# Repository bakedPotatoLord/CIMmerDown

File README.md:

# CIMmer Down
A project to control 2 drive 2 rev robotics spark ESCs from an arduino nano. 

Coming out of a desire to make use of obsolete parts used by FIRST robotics teams worldwide, we designed a low-cost open source electric longboard. Designed to be accessible to high-school and college students to build, using mostly 3d printed and COTS parts, this project aims to provide an interesting and fun entry into the world of RF electronics, motor control, urethane molding, and more. 

Documentation/Development are not yet complete. Help is always appreciated.

## Features
- Handheld remote
- Status LED
- 2 speed modes
- 16mph top speed
- People of the oposite sex may find you more attractive.
- Disconnection detection and e-stop safety.

## More Details

further, yet incomplete documentation can be found at these pages:

- [Electronics](/Electronics.md)
- [Manufacturing](/Manufacturing.md)

## Selected Media

## Why is is called that?
the `CIM` from CIMmer down is a reference to FRC [CIM](https://andymark.com/products/2-5-in-cim-motor) motor.

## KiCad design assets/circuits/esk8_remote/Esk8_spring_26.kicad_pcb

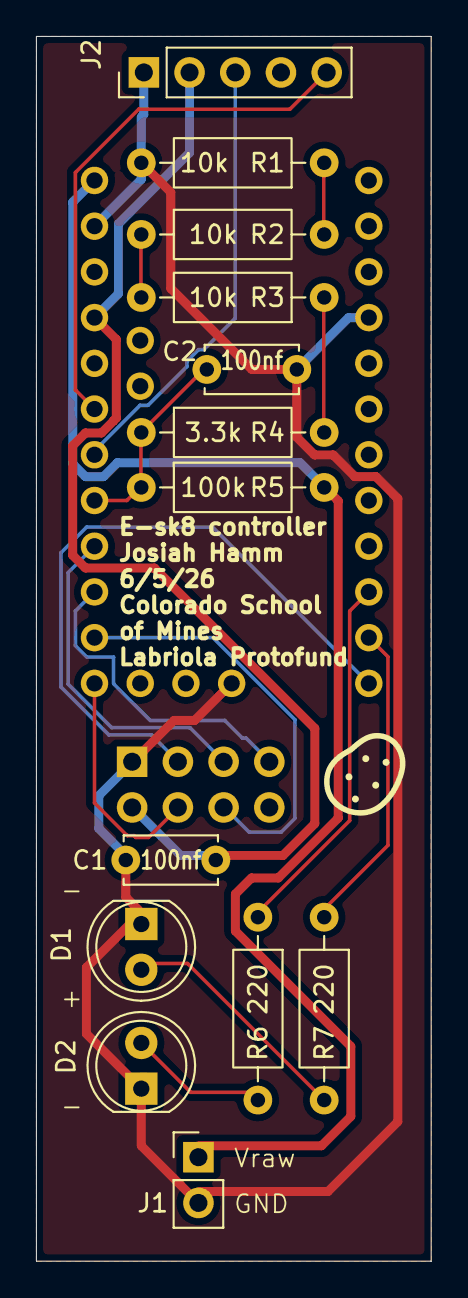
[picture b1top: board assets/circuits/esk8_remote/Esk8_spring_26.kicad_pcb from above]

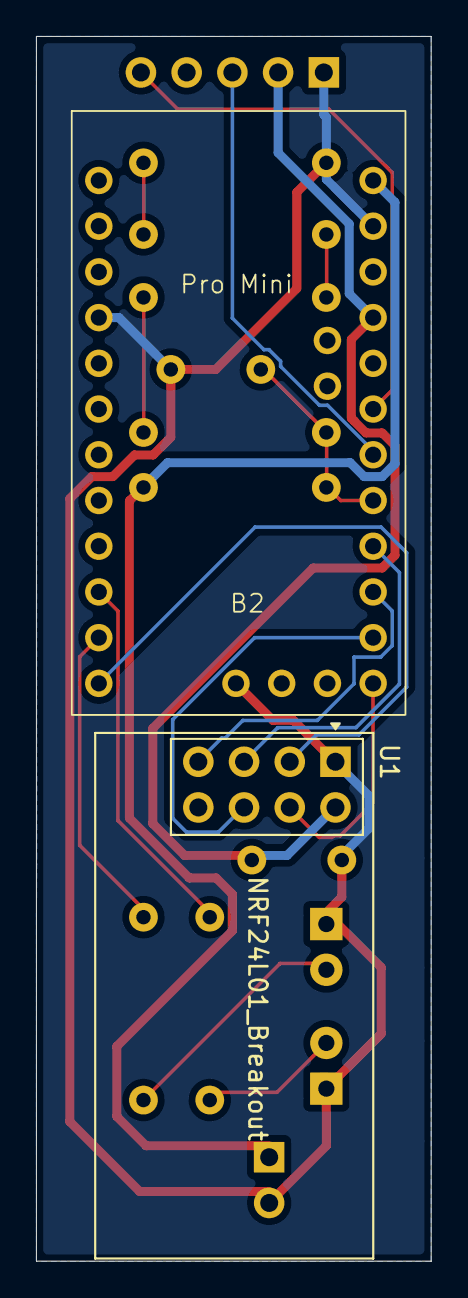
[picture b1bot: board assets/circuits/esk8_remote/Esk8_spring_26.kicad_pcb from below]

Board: 2 copper layers, 21.9 x 68.0 mm, 15 parts (2 on the bottom side), 18 nets.

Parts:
B2: ARDUINO_PRO_MINI; ProMini
C1, C2: 100nf; C_Disc_D5.0mm_W2.5mm_P5.00mm
D1, D2: CHIP-FLAT-B_0603-0.35MM; LED_D5.0mm
J1: Conn_01x02_Pin; PinHeader_1x02_P2.54mm_Vertical
J2: Conn_01x05_Pin; PinHeader_1x05_P2.54mm_Vertical
R1, R2, R3: 10k; R_Axial_DIN0207_L6.3mm_D2.5mm_P10.16mm_Horizontal
R4: 3.3k; R_Axial_DIN0207_L6.3mm_D2.5mm_P10.16mm_Horizontal
R5: 100k; R_Axial_DIN0207_L6.3mm_D2.5mm_P10.16mm_Horizontal
R6, R7: 220; R_Axial_DIN0207_L6.3mm_D2.5mm_P10.16mm_Horizontal
U1: NRF24L01_Breakout; nRF24L01_Breakout

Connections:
+3.3V: B2.21 (VCC), C1.1, J2.2, U1.2 (VCC)
/CE: B2.12 (*9), U1.3 (CE)
/CSN: B2.13 (*10), U1.4 (~CSN)
/MISO: B2.15 (12), U1.7 (MISO)
/MOSI: B2.14 (*11), U1.6 (MOSI)
/SCK: B2.16 (13), U1.5 (SCK)
/SW: B2.19 (A2), J2.5
/VDIV: B2.17 (A0), C2.1, R4.1, R5.1
/VRX: B2.18 (A1), J2.3
GND: B2.4 (GND), B2.23 (GND@2), C1.2, C2.2, D1.1 (K), D2.1 (K), J1.2, J2.1, R1.2, U1.1 (GND)
unnamed: B2.10 (7), R6.1
unnamed: B2.11 (8), R7.1
unnamed: B2.24 (RAW), J1.1, R5.2
unnamed: D1.2 (A), R7.2
unnamed: D2.2 (A), R6.2
unnamed: R1.1, R2.2
unnamed: R2.1, R3.2
unnamed: R3.1, R4.2

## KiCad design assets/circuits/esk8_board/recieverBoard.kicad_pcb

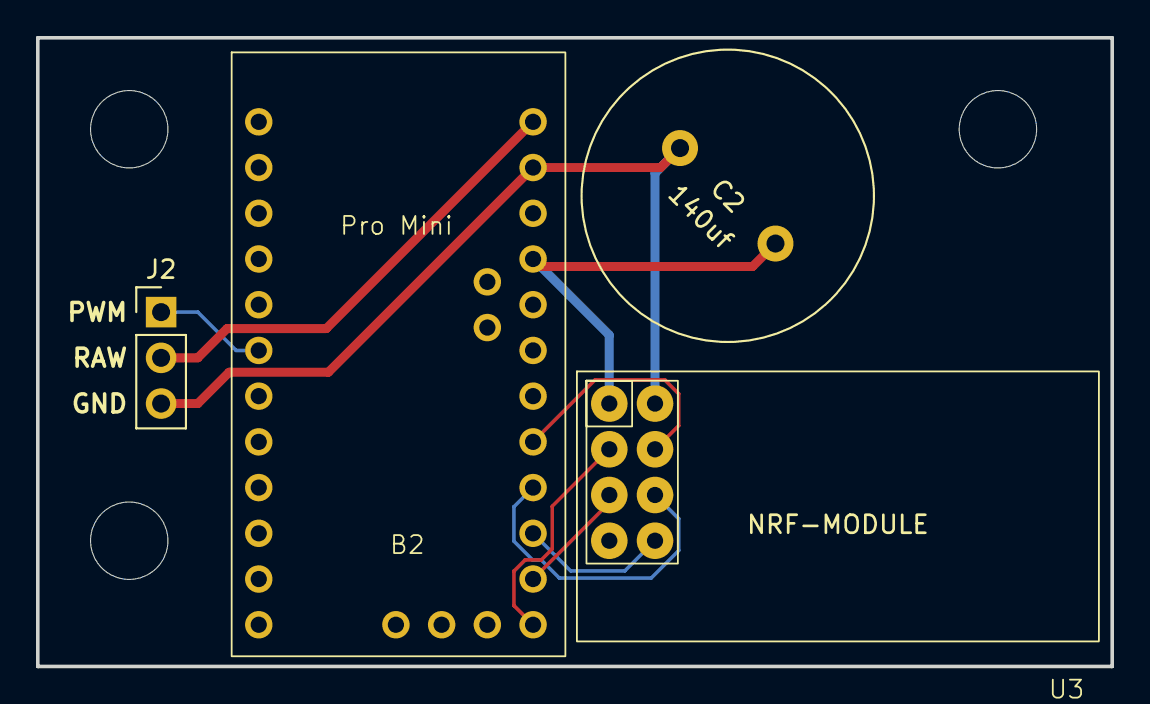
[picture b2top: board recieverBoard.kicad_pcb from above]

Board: 2 copper layers, 59.7 x 34.9 mm, 7 parts (0 on the bottom side), 9 nets.

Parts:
B2: ARDUINO_PRO_MINI; ProMini
C2: 140uf; C_Radial_D16.0mm_H31.5mm_P7.50mm
H1, H2, H3: MountingHole; MountingHole_4.3mm_M4
J2: Conn_01x03_Pin; PinHeader_1x03_P2.54mm_Vertical
U3: NRF-MODULE; NRF24Lo1

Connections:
+3.3V: B2.21 (VCC), C2.2, U3.1 (VCC)
/<NO NET>: B2.14 (*11), U3.5 (MOSI)
/CE: B2.17 (A0), U3.4 (CE)
/CSN: B2.13 (*10), U3.3 (CSN)
/MISO: B2.15 (12), U3.8 (MISO)
/SCK: B2.16 (13), U3.6 (SCK)
GND: B2.23 (GND@2), C2.1, J2.3, U3.2 (GND)
unnamed: B2.6 (*3), J2.1
unnamed: B2.24 (RAW), J2.2

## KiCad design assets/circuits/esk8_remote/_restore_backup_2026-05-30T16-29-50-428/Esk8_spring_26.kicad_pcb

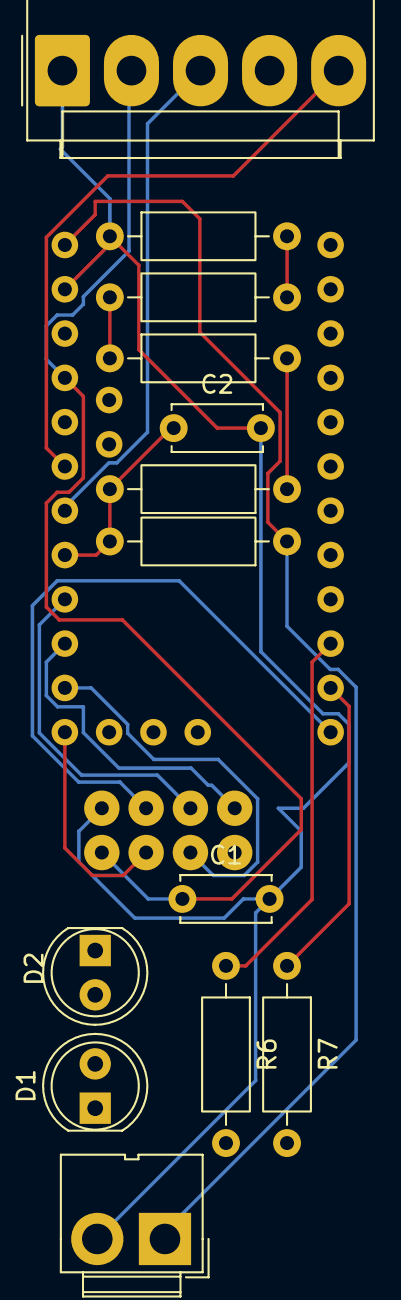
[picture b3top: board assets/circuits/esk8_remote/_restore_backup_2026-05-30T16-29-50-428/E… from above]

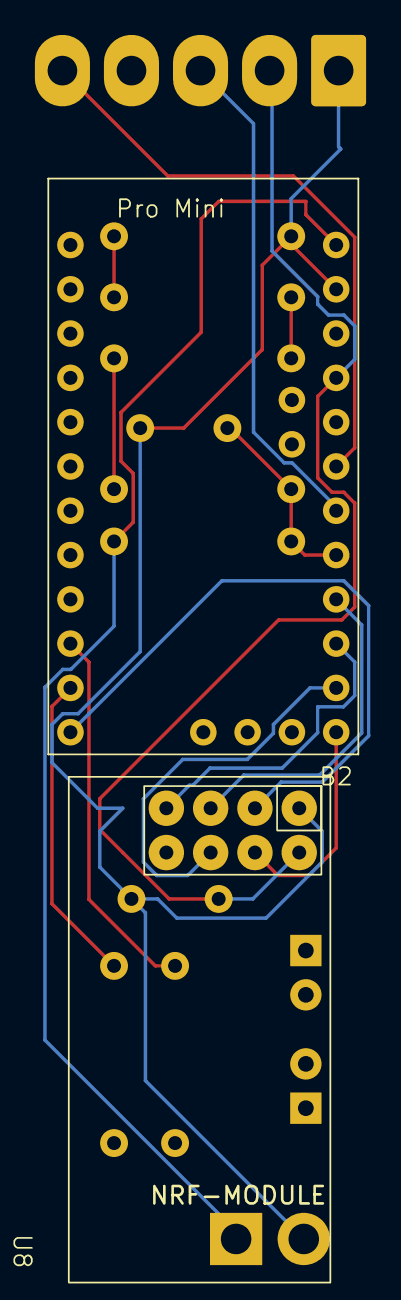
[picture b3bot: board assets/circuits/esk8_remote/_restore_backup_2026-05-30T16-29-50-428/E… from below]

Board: 2 copper layers, 15 parts (2 on the bottom side), 16 nets.

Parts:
B2: ARDUINO_PRO_MINI; ProMini
C1, C2: 100uf; C_Disc_D5.0mm_W2.5mm_P5.00mm
D1, D2: CHIP-FLAT-B_0603-0.35MM; LED_D5.0mm
J1: Conn_01x02_Pin; JWT_A3963_1x02_P3.96mm_Vertical
J2: Conn_01x05_Pin; Molex_KK-396_A-41791-0005_1x05_P3.96mm_Vertical
R1, R2, R3: 10k; R_Axial_DIN0207_L6.3mm_D2.5mm_P10.16mm_Horizontal
R4: 3.3k; R_Axial_DIN0207_L6.3mm_D2.5mm_P10.16mm_Horizontal
R5: 100k; R_Axial_DIN0207_L6.3mm_D2.5mm_P10.16mm_Horizontal
R6, R7: 220; R_Axial_DIN0207_L6.3mm_D2.5mm_P10.16mm_Horizontal
U8: NRF-MODULE; NRF24Lo1

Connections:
+3.3V: B2.21 (VCC), C1.1, J2.2, U8.2 (VCC)
GND: B2.23 (GND@2), C1.2, C2.2, J1.2, J2.1, R1.1, U8.1 (GND)
unnamed: B2.10 (7), R6.1
unnamed: B2.11 (8), R7.1
unnamed: B2.15 (12), U8.7 (MISO)
unnamed: B2.16 (13), U8.5 (SCK)
unnamed: B2.12 (*9), U8.3 (CE)
unnamed: B2.13 (*10), U8.4 (CSN)
unnamed: B2.14 (*11), U8.6 (MOSI)
unnamed: B2.17 (A0), C2.1, R4.2, R5.2
unnamed: B2.18 (A1), J2.3
unnamed: B2.19 (A2), J2.5
unnamed: B2.24 (RAW), J1.1, R5.1
unnamed: R1.2, R2.1
unnamed: R2.2, R3.1
unnamed: R3.2, R4.1

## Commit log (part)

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2025-08-27 Current Code V1.1
2025-08-31 move into it's own folder
2025-09-01 quicksave
2025-09-01 finalize encoder code
2025-09-03 add picture of progress
2025-11-12 add safety features
2025-11-12 fix typo
2025-12-18 split to modular chunks
2025-12-18 init pio
2025-12-18 switch to pio best practices
2025-12-19 basic RF functionality
2025-12-19 basic payload transmission
2025-12-19 wheels spinning
2025-12-20 increase polling freqency
2025-12-20 rename rf to controller
2025-12-20 add debug and mute ifdefs
2025-12-20 rename rfloop -> controllerloop
2025-12-25 switch configs to both pro minis
2025-12-27 reconfigure for voltage divider and transistor buzzer
2025-12-27 add more debug prints
2025-12-27 remove vsc meta
2025-12-27 add recomended extentions
2025-12-27 add controller vdiv code
2026-01-06 read battery
2026-01-06 add speed debug print
2026-01-07 add prod deployment configs
2026-01-07 first pass at status LED
2026-01-07 go to await mode if not recieved in 2s
2026-01-07 switch const names
2026-01-08 start on electronics docs
2026-01-08 remove outdated svg
2026-01-08 start electronics docs
2026-03-15 add vescUart and get connected
2026-03-15 switch to PWM because the VESC is a liar
2026-03-27 add led 2 pin define
2026-03-28 make remote specfic
2026-04-07 end unending while if hardware not responding
2026-04-09 update vdiv
2026-04-09 add software multiplier and remove buzzer
2026-04-09 switch to arduino nano for board
2026-04-09 get blue and red LEDs working
2026-04-29 switch to correct arduino board
2026-05-03 combine both boards in one branch
2026-05-05 making address configurable
2026-05-05 add remote config
2026-05-05 move cycle freq to shared header
2026-05-05 create ramp rate
2026-05-29 add 3d printing files
2026-05-29 move assets to assets folder
2026-05-29 complete first two sections of manufacturing
2026-05-30 revert ramp rate code. needs encoder to work properly.
2026-05-31 add kicad circuit
2026-05-31 complete manufacturing guide
2026-05-31 complete readme
